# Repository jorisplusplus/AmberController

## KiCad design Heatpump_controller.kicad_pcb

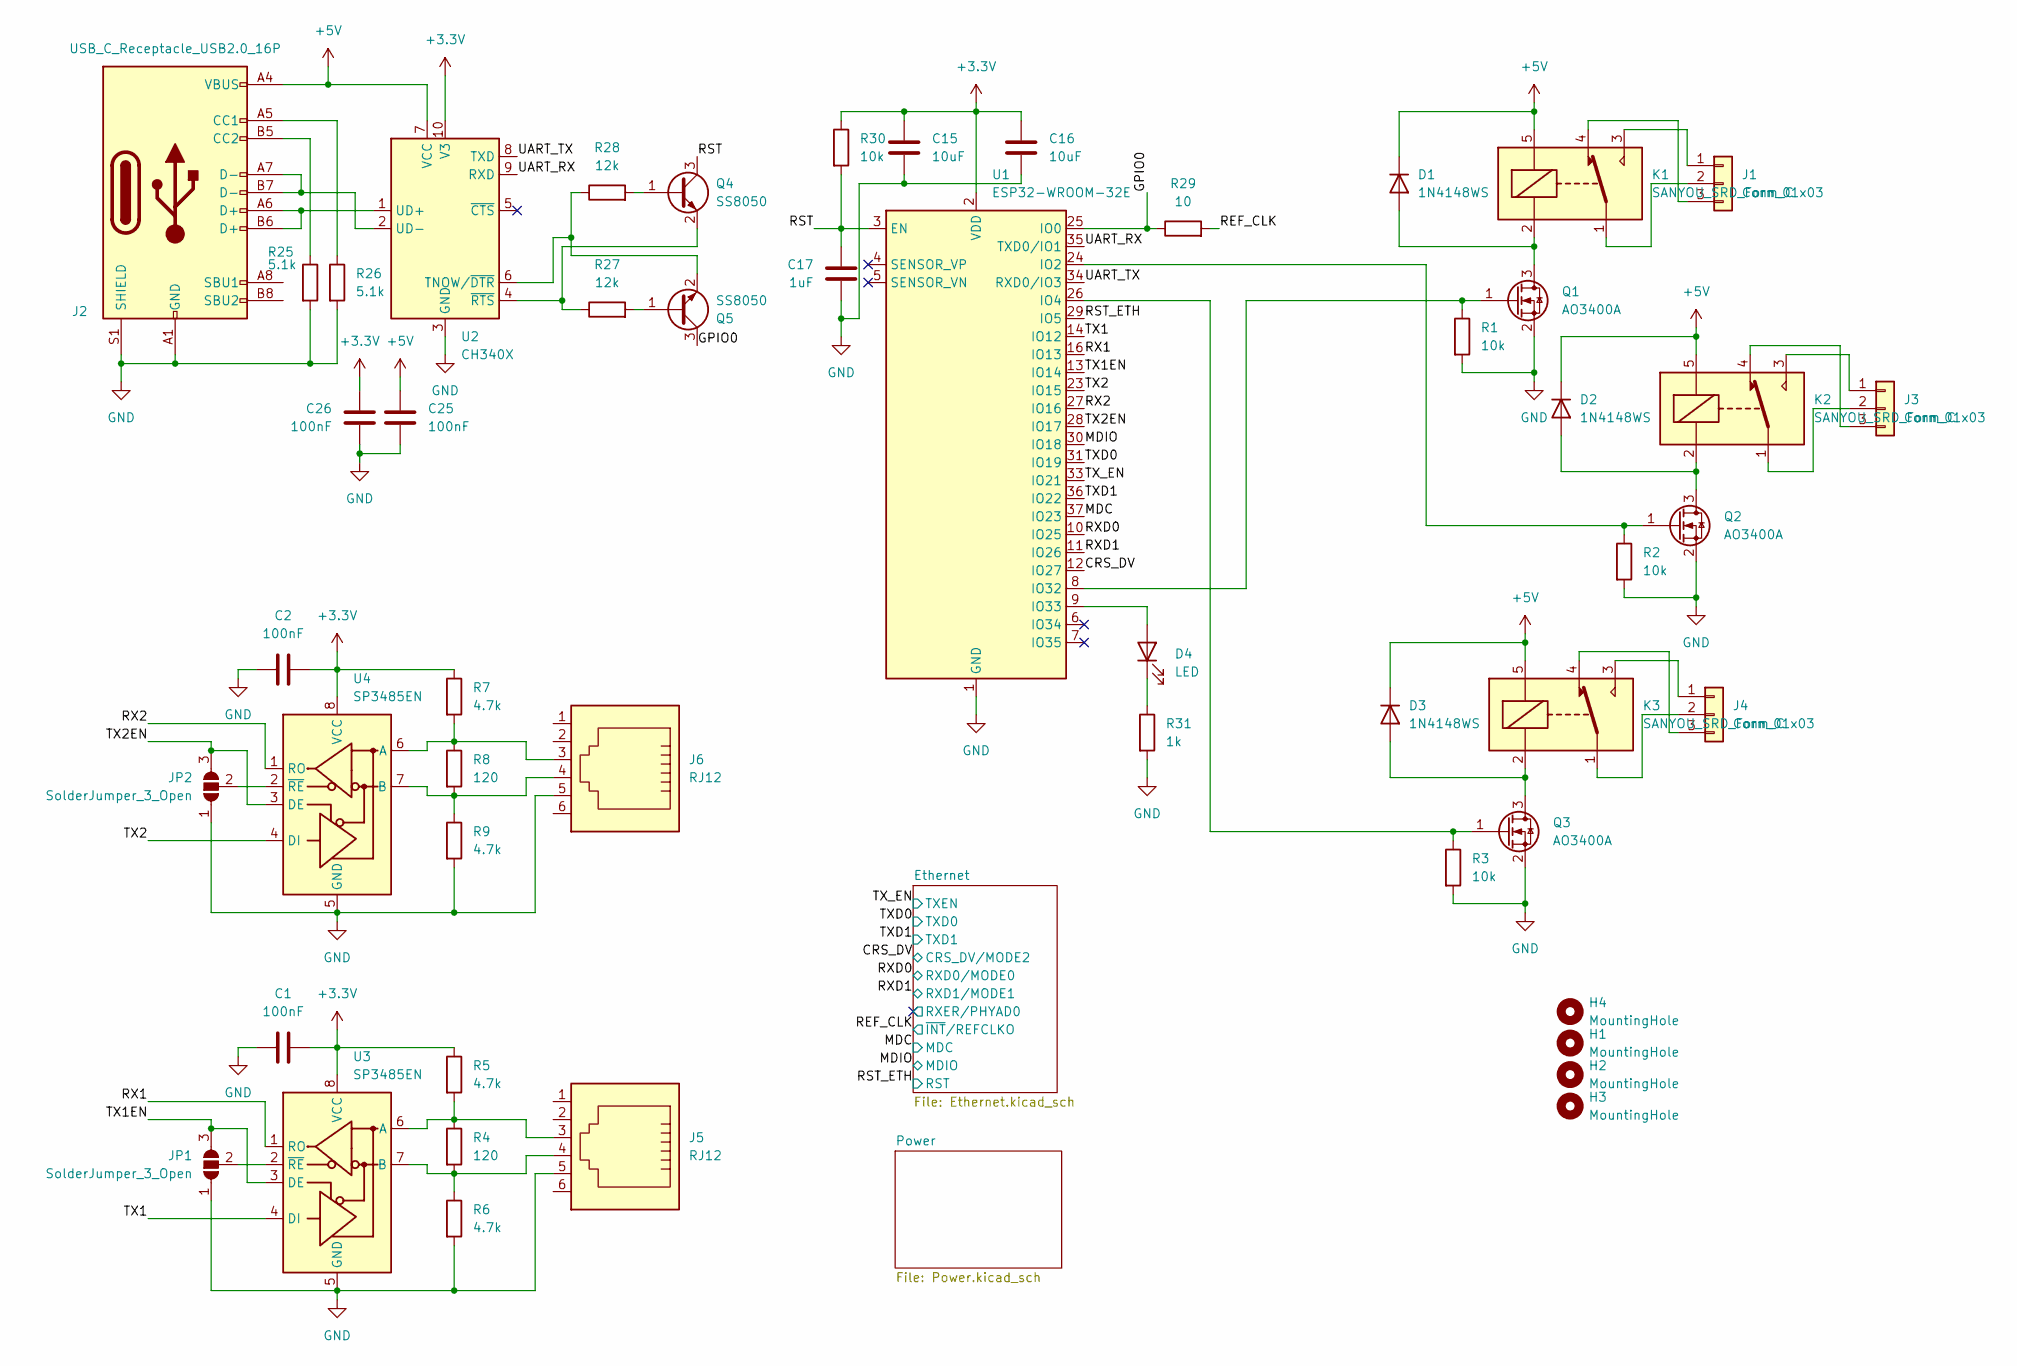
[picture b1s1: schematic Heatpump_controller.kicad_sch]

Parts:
C1, C2, C25, C26: 100nF; C_0603_1608Metric
C15, C16: 10uF; C_0805_2012Metric
C17: 1uF; C_0805_2012Metric
D1, D2, D3: 1N4148WS; D_SOD-323
D4: LED; LED_0805_2012Metric
H1, H2, H3, H4: MountingHole; MountingHole_3.2mm_M3
J1, J3, J4: Conn_01x03; TerminalBlock_Phoenix_MKDS-1,5-3-5.08_1x03_P5.08mm_Horizont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
J2: USB_C_Receptacle_USB2.0_16P; USB_C_Receptacle_HRO_TYPE-C-31-M-12
J5, J6: RJ12; RJ12_Amphenol_54601-x06_Horizontal
JP1, JP2: SolderJumper_3_Open; SolderJumper-3_P1.3mm_Open_RoundedPad1.0x1.5mm
K1, K2, K3: SANYOU_SRD_Form_C; Relay_SPDT_SANYOU_SRD_Series_Form_C
Q1, Q2, Q3: AO3400A; SOT-23
Q4, Q5: SS8050; SOT-23
R1, R2, R3, R30: 10k; R_0603_1608Metric
R4, R8: 120; R_0603_1608Metric
R5, R6, R7, R9: 4.7k; R_0603_1608Metric
R25, R26: 5.1k; R_0603_1608Metric
R27, R28: 12k; R_0603_1608Metric
R29: 10; R_0603_1608Metric
R31: 1k; R_0603_1608Metric
U1: ESP32-WROOM-32E; ESP32-WROOM-32D
U2: CH340X; MSOP-10_3x3mm_P0.5mm
U3, U4: SP3485EN; SOIC-8_3.9x4.9mm_P1.27mm

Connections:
+3.3V: C1.2, C2.2, C15.1, C16.1, C26.2, R5.1, R7.1, R30.1, U1.2 (VDD), U2.10 (V3), U3.8 (VCC), U4.8 (VCC); also elsewhere on the board
+5V: C25.2, D1.1 (K), D2.1 (K), D3.1 (K), J2.A4 (VBUS), J2.A9 (VBUS), J2.B4 (VBUS), J2.B9 (VBUS), K1.5, K2.5, K3.5, U2.7 (VCC); also elsewhere on the board
/CRS_DV: U1.12 (IO27); also elsewhere on the board
/GPIO0: Q5.3 (C), R29.1, U1.25 (IO0)
/MDC: U1.37 (IO23); also elsewhere on the board
/MDIO: U1.30 (IO18); also elsewhere on the board
/REF_CLK: R29.2; also elsewhere on the board
/RST: C17.1, Q4.3 (C), R30.2, U1.3 (EN)
/RST_ETH: U1.29 (IO5); also elsewhere on the board
/RX1: U1.16 (IO13), U3.1 (RO)
/RX2: U1.27 (IO16), U4.1 (RO)
/RXD0: U1.10 (IO25); also elsewhere on the board
/RXD1: U1.11 (IO26); also elsewhere on the board
/TX1: U1.14 (IO12), U3.4 (DI)
/TX1EN: JP1.3 (B), U1.13 (IO14), U3.3 (DE)
/TX2: U1.23 (IO15), U4.4 (DI)
/TX2EN: JP2.3 (B), U1.28 (IO17), U4.3 (DE)
/TXD0: U1.31 (IO19); also elsewhere on the board
/TXD1: U1.36 (IO22); also elsewhere on the board
/TX_EN: U1.33 (IO21); also elsewhere on the board
/UART_RX: U1.35 (TXD0/IO1), U2.9 (RXD)
/UART_TX: U1.34 (RXD0/IO3), U2.8 (TXD)
GND: C1.1, C2.1, C15.2, C16.2, C17.2, C25.1, C26.1, J2.A1 (GND), J2.A12 (GND), J2.B1 (GND), J2.B12 (GND), J2.S1 (SHIELD), J5.5, J6.5, JP1.1 (A), JP2.1 (A), Q1.2 (S), Q2.2 (S), Q3.2 (S), R1.2, R2.2, R3.2, R6.2, R9.2, R25.2, R26.2, R31.2, U1.1 (GND), U1.15 (GND), U1.38 (GND), U1.39 (GND), U2.3 (GND), U3.5 (GND), U4.5 (GND); also elsewhere on the board
unnamed: D1.2 (A), K1.2, Q1.3 (D)
unnamed: D2.2 (A), K2.2, Q2.3 (D)
unnamed: D3.2 (A), K3.2, Q3.3 (D)
unnamed: D4.2 (A), U1.9 (IO33)
unnamed: D4.1 (K), R31.1
unnamed: J1.1, K1.3
unnamed: J1.2, K1.1
unnamed: J1.3, K1.4
unnamed: J2.A5 (CC1), R26.1
unnamed: J2.B5 (CC2), R25.1
unnamed: J3.1, K2.3
unnamed: J3.2, K2.1
unnamed: J3.3, K2.4
unnamed: J4.1, K3.3
unnamed: J4.2, K3.1
unnamed: J4.3, K3.4
unnamed: JP1.2 (C), U3.2 (~RE)
unnamed: JP2.2 (C), U4.2 (~RE)
unnamed: Q1.1 (G), R1.1, U1.8 (IO32)
unnamed: Q2.1 (G), R2.1, U1.24 (IO2)
unnamed: Q3.1 (G), R3.1, U1.26 (IO4)
unnamed: Q4.1 (B), R28.2
unnamed: Q4.2 (E), R27.1, U2.4 (~RTS)
unnamed: Q5.1 (B), R27.2
unnamed: Q5.2 (E), R28.1, U2.6 (TNOW/~DTR)
unnamed: J2.A6 (D+), J2.B6 (D+), U2.1 (UD+)
unnamed: J2.A7 (D-), J2.B7 (D-), U2.2 (UD-)
unnamed: J5.3, R4.1, R5.2, U3.6 (A)
unnamed: J5.4, R4.2, R6.1, U3.7 (B)
unnamed: J6.3, R7.2, R8.1, U4.6 (A)
unnamed: J6.4, R8.2, R9.1, U4.7 (B)

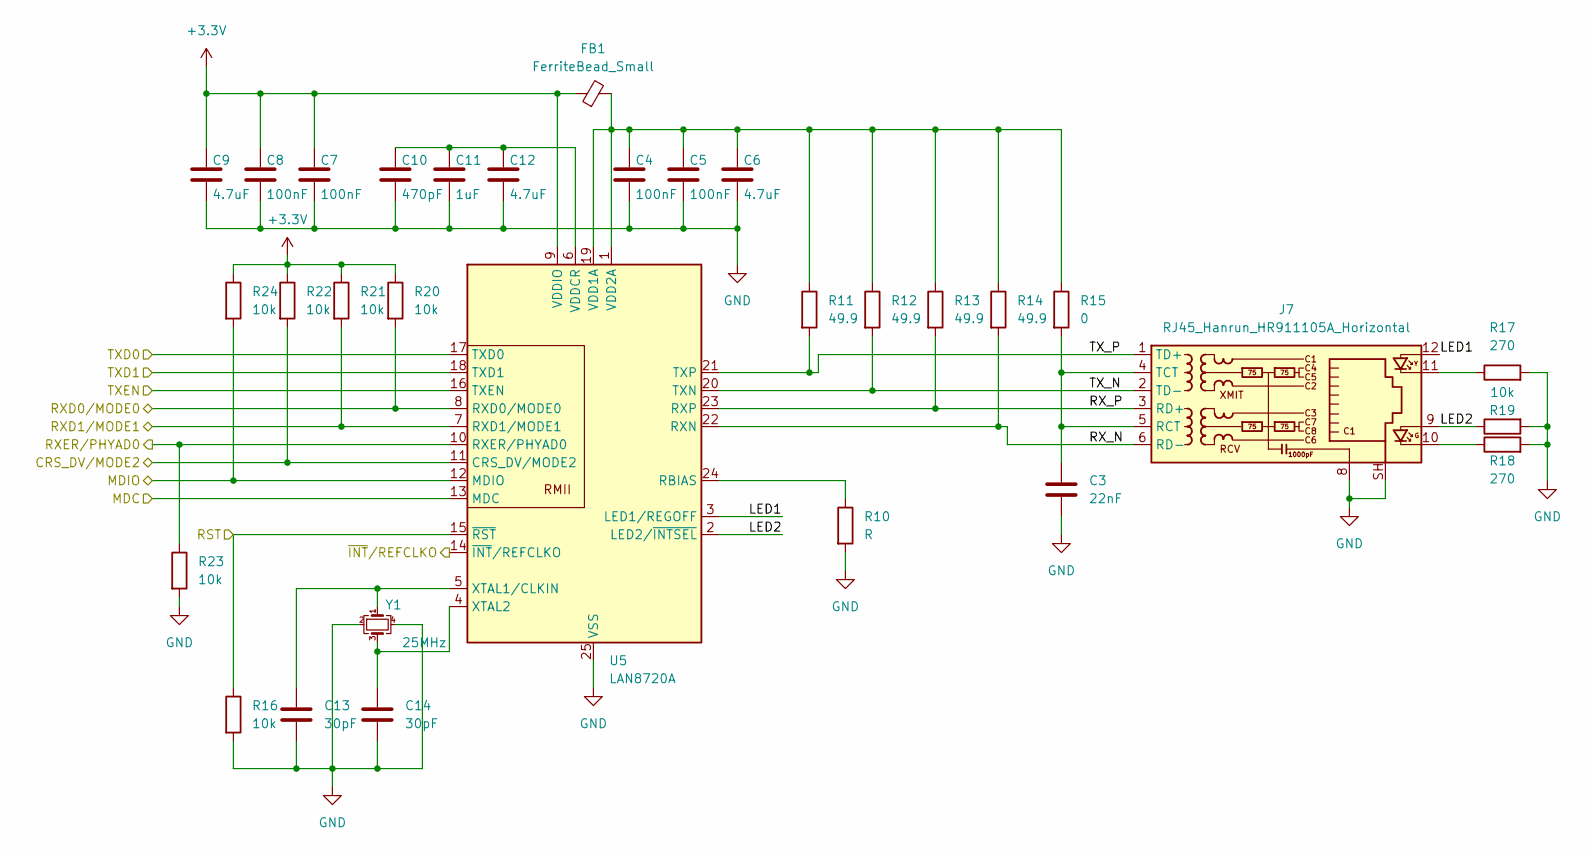
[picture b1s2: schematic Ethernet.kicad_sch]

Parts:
C3: 22nF; C_0603_1608Metric
C4, C5, C7, C8: 100nF; C_0603_1608Metric
C6, C9, C12: 4.7uF; C_0805_2012Metric
C10: 470pF; C_0603_1608Metric
C11: 1uF; C_0805_2012Metric
C13, C14: 30pF; C_0603_1608Metric
FB1: FerriteBead_Small; L_0603_1608Metric
J7: RJ45_Hanrun_HR911105A_Horizontal
R10: R; R_0603_1608Metric
R11, R12, R13, R14: 49.9; R_0603_1608Metric
R15: 0; R_0603_1608Metric
R16, R19, R20, R21, R22, R23, R24: 10k; R_0603_1608Metric
R17, R18: 270; R_0603_1608Metric
U5: LAN8720A; VQFN-24-1EP_4x4mm_P0.5mm_EP2.5x2.5mm_ThermalVias
Y1: 25MHz; Crystal_SMD_3225-4Pin_3.2x2.5mm

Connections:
+3.3V: C7.1, C8.1, C9.1, FB1.1, R20.1, R21.1, R22.1, R24.1, U5.9 (VDDIO); also elsewhere on the board
/CRS_DV: R22.2, U5.11 (CRS_DV/MODE2); also elsewhere on the board
/Ethernet/LED1: J7.12, U5.3 (LED1/REGOFF)
/Ethernet/LED2: J7.9, R19.1, U5.2 (LED2/~INTSEL)
/Ethernet/RXER/PHYAD0: R23.1, U5.10 (RXER/PHYAD0)
/Ethernet/RX_N: J7.6 (RD-), R14.2, U5.22 (RXN)
/Ethernet/RX_P: J7.3 (RD+), R13.2, U5.23 (RXP)
/Ethernet/TX_N: J7.2 (TD-), R12.2, U5.20 (TXN)
/Ethernet/TX_P: J7.1 (TD+), R11.2, U5.21 (TXP)
/MDC: U5.13 (MDC); also elsewhere on the board
/MDIO: R24.2, U5.12 (MDIO); also elsewhere on the board
/REF_CLK: U5.14 (~INT/REFCLKO); also elsewhere on the board
/RST_ETH: R16.1, U5.15 (~RST); also elsewhere on the board
/RXD0: R20.2, U5.8 (RXD0/MODE0); also elsewhere on the board
/RXD1: R21.2, U5.7 (RXD1/MODE1); also elsewhere on the board
/TXD0: U5.17 (TXD0); also elsewhere on the board
/TXD1: U5.18 (TXD1); also elsewhere on the board
/TX_EN: U5.16 (TXEN); also elsewhere on the board
GND: C3.2, C4.2, C5.2, C6.2, C7.2, C8.2, C9.2, C10.2, C11.2, C12.2, C13.2, C14.2, J7.8, J7.SH, R10.2, R16.2, R17.2, R18.2, R19.2, R23.2, U5.25 (VSS), Y1.2, Y1.4; also elsewhere on the board
unnamed: J7.10, R18.1
unnamed: J7.11, R17.1
unnamed: C3.1, J7.4 (TCT), J7.5 (RCT), R15.2
unnamed: R10.1, U5.24 (RBIAS)
unnamed: C4.1, C5.1, C6.1, FB1.2, R11.1, R12.1, R13.1, R14.1, R15.1, U5.1 (VDD2A), U5.19 (VDD1A)
unnamed: C10.1, C11.1, C12.1, U5.6 (VDDCR)
unnamed: C13.1, U5.5 (XTAL1/CLKIN), Y1.1
unnamed: C14.1, U5.4 (XTAL2), Y1.3

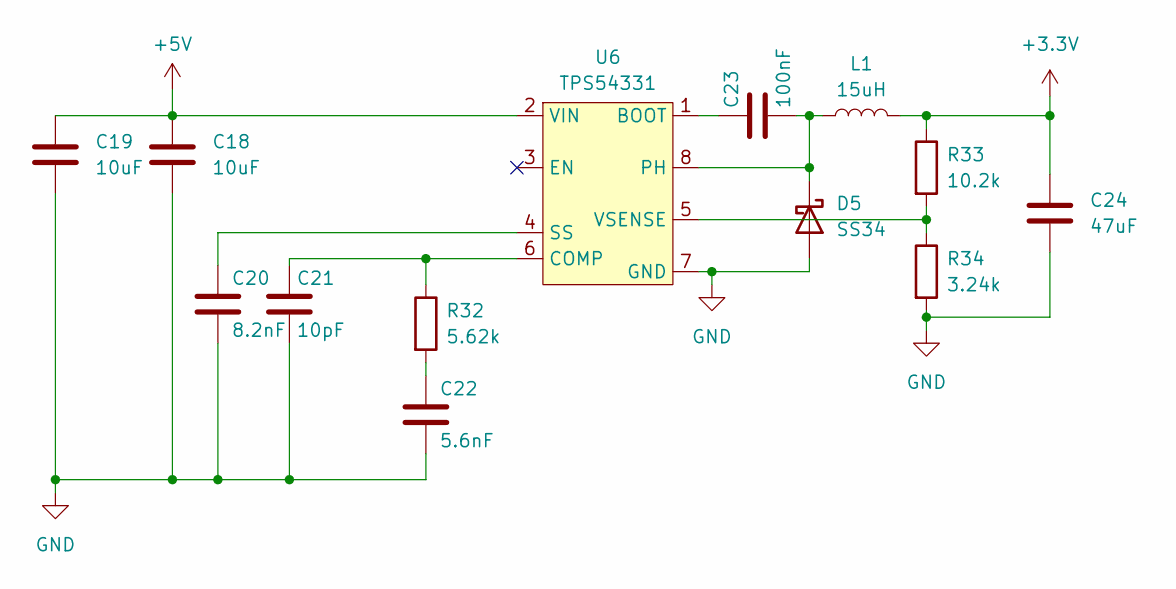
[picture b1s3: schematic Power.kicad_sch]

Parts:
C18, C19: 10uF; C_0805_2012Metric
C20: 8.2nF; C_0603_1608Metric
C21: 10pF; C_0603_1608Metric
C22: 5.6nF; C_0603_1608Metric
C23: 100nF; C_0603_1608Metric
C24: 47uF; C_0805_2012Metric
D5: SS34; D_SMA
L1: 15uH; L_Changjiang_FXL0630; LCSC C177243
R32: 5.62k; R_0603_1608Metric
R33: 10.2k; R_0603_1608Metric
R34: 3.24k; R_0603_1608Metric
U6: TPS54331; SOIC-8_3.9x4.9mm_P1.27mm

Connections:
+3.3V: C24.1, L1.2, R33.1; also elsewhere on the board
+5V: C18.1, C19.1, U6.2 (VIN); also elsewhere on the board
GND: C18.2, C19.2, C20.2, C21.2, C22.2, C24.2, D5.2 (A), R34.2, U6.7 (GND); also elsewhere on the board
unnamed: C22.1, R32.2
unnamed: C23.2, D5.1 (K), L1.1, U6.8 (PH)
unnamed: C23.1, U6.1 (BOOT)
unnamed: C21.1, R32.1, U6.6 (COMP)
unnamed: C20.1, U6.4 (SS)
unnamed: R33.2, R34.1, U6.5 (VSENSE)

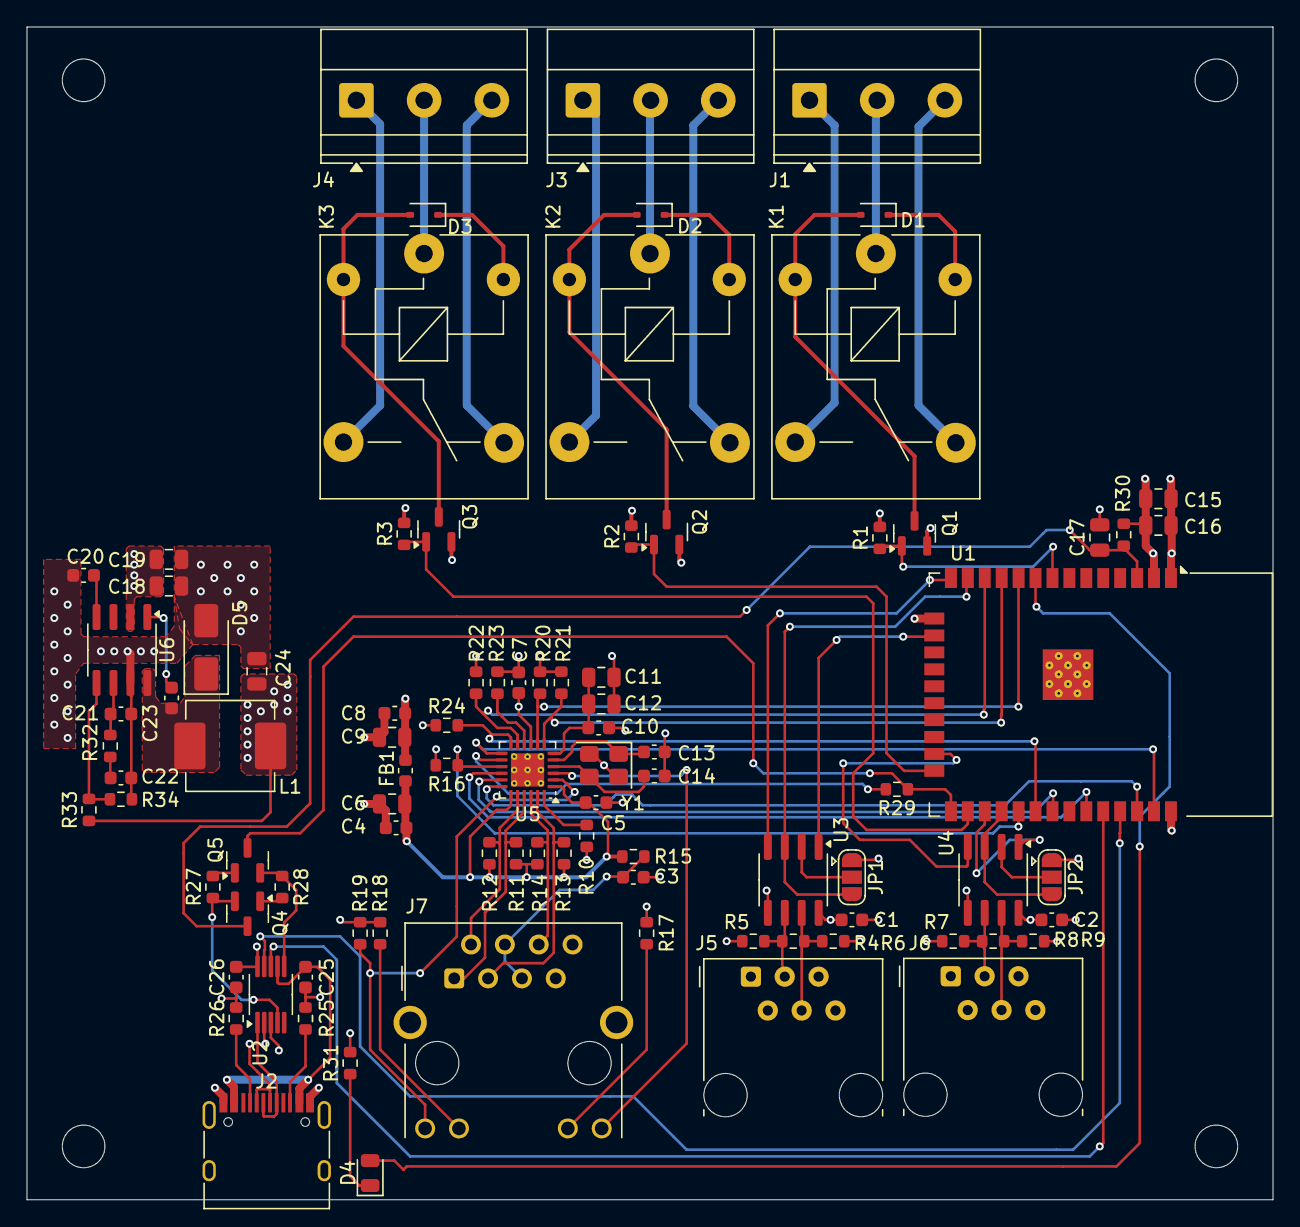
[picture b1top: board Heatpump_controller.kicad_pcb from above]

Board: 4 copper layers, 93.5 x 88.0 mm, 95 parts (0 on the bottom side), 75 nets.

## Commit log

2025-10-14 Initial HW design
2025-10-14 Added PCB outline
2025-10-17 Finished route
2025-10-17 Added lcsc power numbers
